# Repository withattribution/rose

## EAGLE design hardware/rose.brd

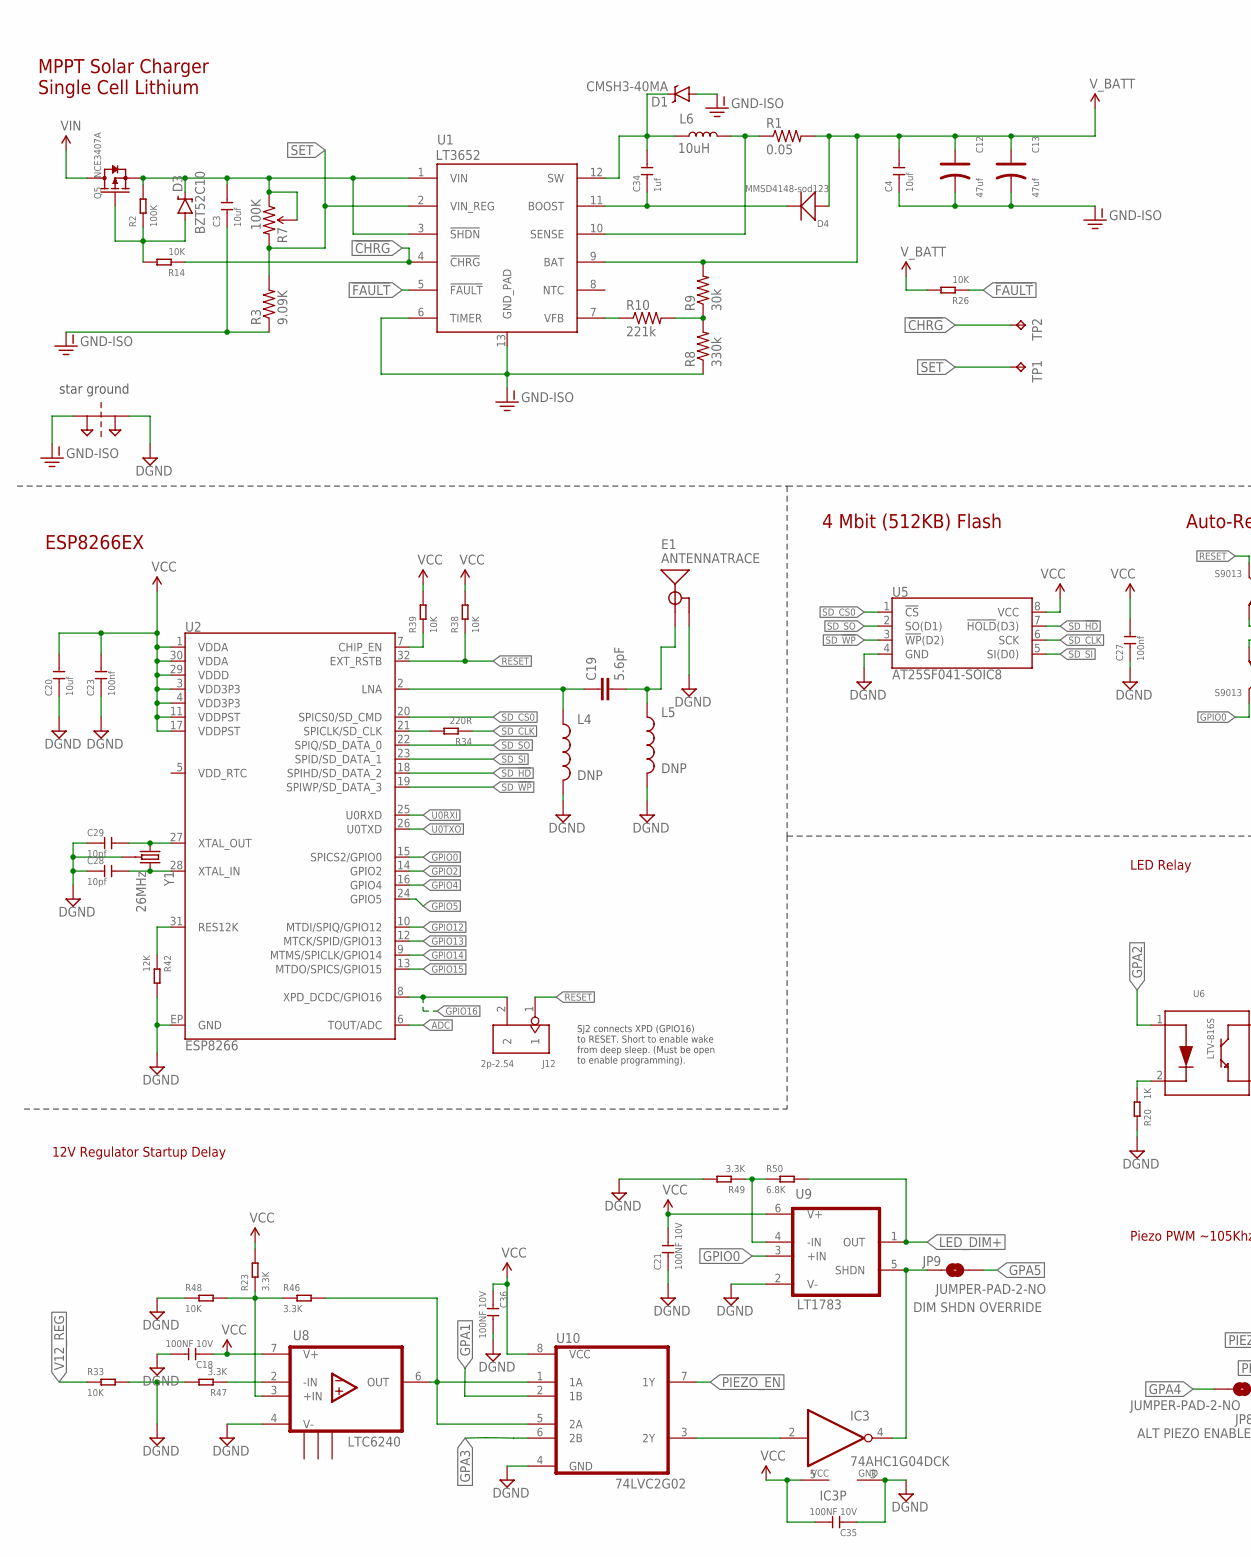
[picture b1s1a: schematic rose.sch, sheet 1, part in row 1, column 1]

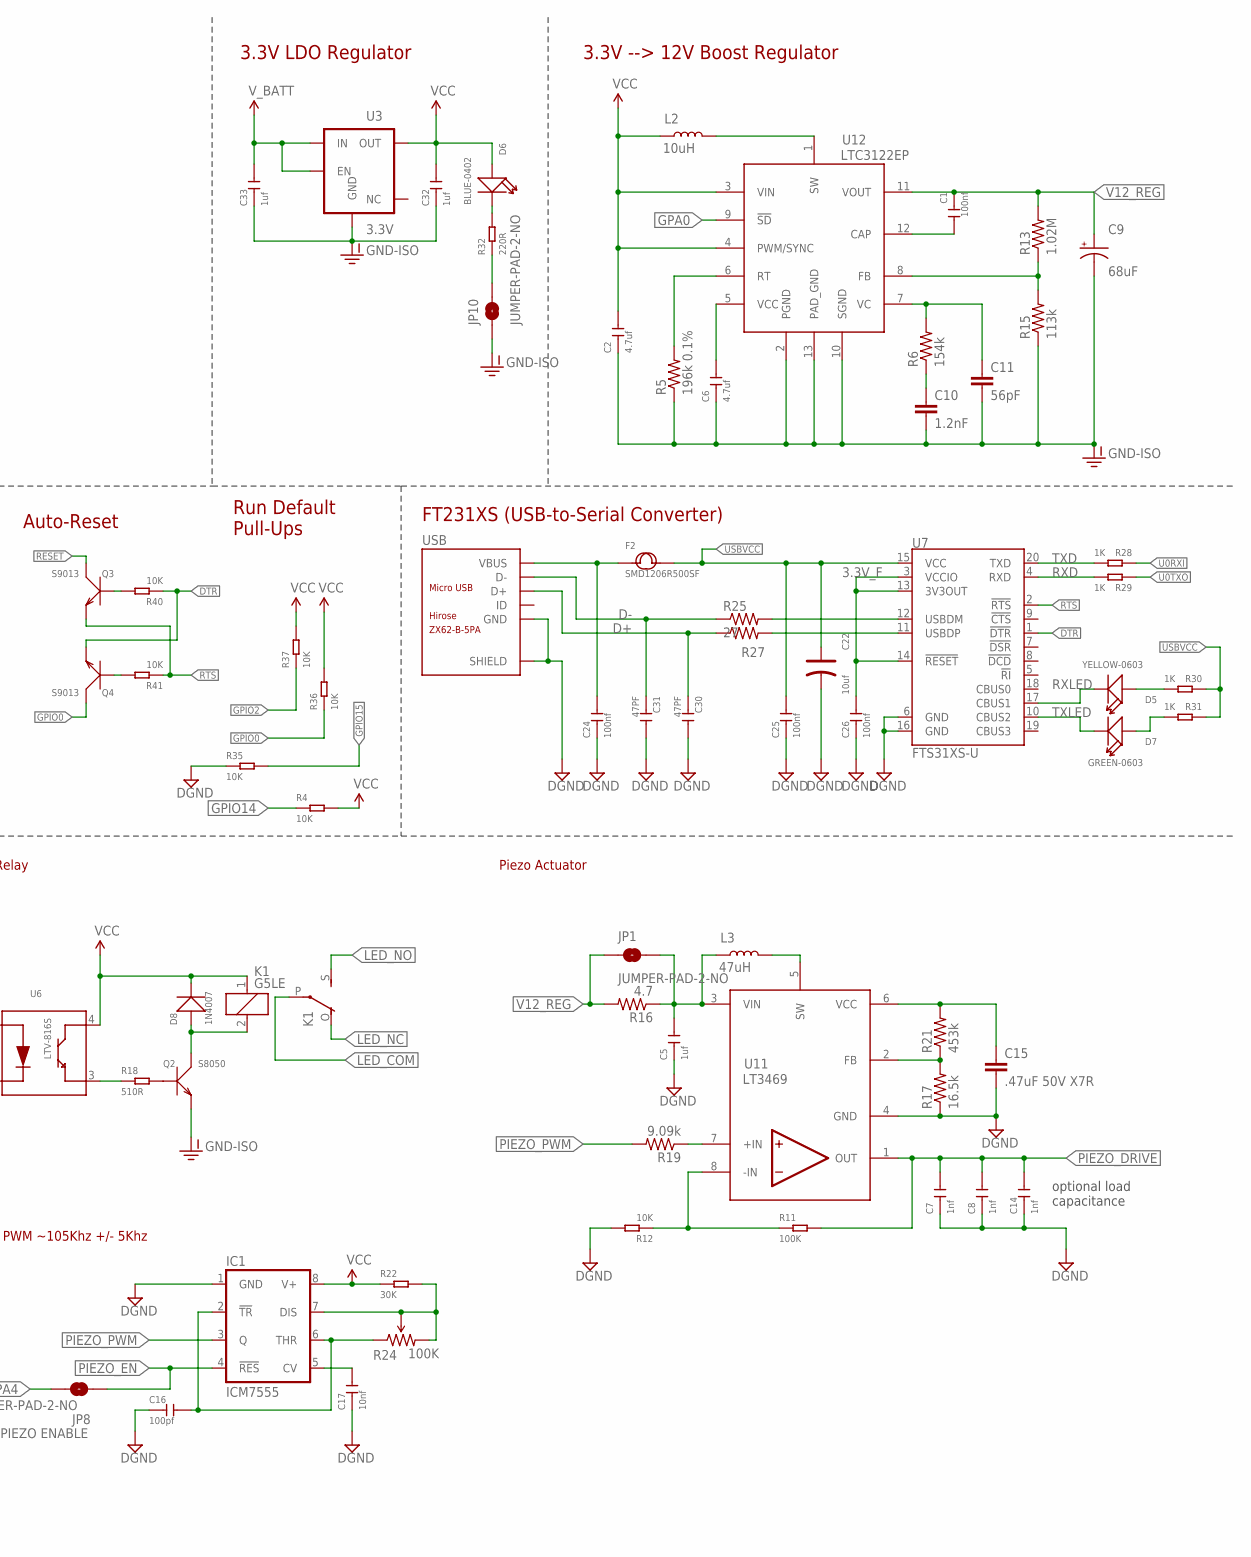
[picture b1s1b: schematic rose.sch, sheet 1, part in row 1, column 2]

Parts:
C1, C23, C24, C25, C26, C27: 100nf; C0402
C2, C6: 4.7uf; C0603
C3, C4: 10uf; C0805
C5, C32, C33, C34: 1uf; C0603
C7, C8, C14: 1nf; C0402
C9: 68uF; EIA6032
C10: 1.2nF; 0603-CAP
C11: 56pF; 0603-CAP
C12, C13: 47uf; AVX-C
C15: .47uF 50V X7R; 0603-CAP
C16: 100pf; C0603
C17: 10nf; C0402
C18, C21, C35, C36: 100NF 10V; C0402
C19: 5.6pF; 0603-CAP
C20: 10uf; C0402
C22: 10uf; AVX-A
C28, C29: 10pf; C0402
C30, C31: 47PF; C0402
D1: CMSH3-40MA; SMA-DIODE
D3: BZT52C10; SOD-123
D4: MMSD4148-sod123; SOD-123
D5: YELLOW-0603; LED-0603
D6: BLUE-0402; LED-0402
D7: GREEN-0603; LED-0603
D8: 1N4007; DO-214AC
E1: ANTENNATRACE; TRACE_ANTENNA_2.4GHZ_25.7MM
F2: SMD1206R500SF; F1206
IC1: ICM7555; SO08
IC3: 74AHC1G04DCK; SC70-5
J12: 2p-2.54; H2-2.54
JP1, JP8, JP9, JP10: JUMPER-PAD-2-NO; PAD-JUMPER-2-NO_NO_SILK
K1: G5LE
L2, L6: 10uH; SRR1240
L3: 47uH; SRR1240
L4, L5: DNP; 0603
PT1: 2PT_GND_TIE
Q2: S8050; SOT-23
Q3, Q4: S9013; SOT-23
Q5: NCE3407A; SOT-23
R1: 0.05; 1206
R2, R11: 100K; R0603
R3: 9.09K; 0603-RES
R4, R12, R14, R26, R33, R35, R36, R37, R38, R39, R40, R41, R48: 10K; R0603
R5: 196k 0.1%; 0603-RES
R6: 154k; 0603-RES
R7, R24: 100K; ST4ETA
R8: 330k; 0603-RES
R9: 30k; 0603-RES
R10: 221k; 0603-RES
R13: 1.02M; 0603-RES
R15: 113k; 0603-RES
R16: 4.7; 0603-RES
R17: 16.5k; 0603-RES
R18: 510R; R0603
R19: 9.09k; 0603-RES
R20, R28, R29, R30, R31: 1K; R0603
R21: 453k; 0603-RES
R22: 30K; R0603
R23, R46, R47, R49: 3.3K; R0603
R25, R27: 27; 0603-RES
R32, R34: 220R; R0603
R42: 12K; R0603
R50: 6.8K; R0603
TP1, TP2: TPTP10SQ; TP10SQ
U1: LT3652; MSOP-12_GND
U2: ESP8266; QFN32
U3: 3.3V; SOT23-5
U5: AT25SF041-SOIC8; SO08
U6: LTV-816S; SMD4-2.54-4.6X6.5MM
U7: FTS31XS-U; SSOP20_L
U8: LTC6240; SOIC-8
U9: LT1783; TSOT-23-6
U10: 74LVC2G02; TSSOP-8
U11: LT3469; TSOT-23-8
U12: LTC3122EP; 12MSOP
USB: ZX62-B-5PA; MICRO-USB5+6P-SMD-0.65-AB
Y1: 26MHz; CRYSTAL-SMD-3.2X2.5

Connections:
3.3V_F: C26.2, U7.3 (VCCIO), U7.13 (3V3OUT), U7.14 (!RESET)
!CHRG: R14.1, TP2.TP, U1.4 (!CHRG)
!FAULT: R26.1, U1.5 (!FAULT)
ADC: U2.6 (TOUT/ADC); also elsewhere on the board
BOOST: C34.1, D4.-, U1.11 (BOOST)
CHIP_EN: R39.1, U2.7 (CHIP_EN)
D+: C30.1, R27.1, USB.3 (D+)
D-: C31.1, R25.1, USB.2 (D-)
DGND: C5.1, C7.1, C8.1, C14.1, C15.2, C16.1, C17.1, C18.2, C20.1, C21.1, C22.-, C23.1, C24.1, C25.1, C26.1, C27.1, C28.1, C29.1, C30.2, C31.2, C35.1, C36.2, E1.GND, E1.GND2 (GND), IC1.1 (GND), IC3.3 (GND), L4.2, L5.2, PT1.P$2, R12.2, R17.1, R20.2, R33.2, R35.1, R42.2, R47.2, R48.1, R49.2, U2.EP (GND), U5.4 (GND), U7.6 (GND), U7.16 (GND), U8.4 (V-), U9.2 (V-), U10.4 (GND), U11.4 (GND), USB.5 (GND), USB.P1 (SHIELD), USB.P2 (SHIELD), USB.P3 (SHIELD), USB.P4 (SHIELD), USB.P5 (SHIELD), USB.P6 (SHIELD), Y1.2 (GND), Y1.4 (GND); also elsewhere on the board
DTR: Q4.2 (E), R40.1, U7.1 (!DTR)
FB: R8.2, R9.1, R10.2
GND-ISO: C2.1, C3.1, C4.1, C6.1, C9.P$2 (-), C10.2, C11.2, C12.-, C13.-, C32.1, C33.1, D1.A, JP10.1, PT1.P$1, Q2.2 (E), R3.1, R5.1, R8.1, R15.1, U1.6 (TIMER), U1.13 (GND_PAD), U3.2 (GND), U12.2 (PGND), U12.10 (SGND), U12.13 (PAD_GND); also elsewhere on the board
GPA0: U12.9 (!SD); also elsewhere on the board
GPA1: U10.2 (1B); also elsewhere on the board
GPA2: U6.1 (ANODE); also elsewhere on the board
GPA3: U10.6 (2B); also elsewhere on the board
GPA4: JP8.1; also elsewhere on the board
GPA5: JP9.1; also elsewhere on the board
GPIO0: Q4.3 (C), R36.1, U2.15 (SPICS2/GPIO0), U9.3 (+IN)
GPIO2: R37.1, U2.14 (GPIO2); also elsewhere on the board
GPIO4: U2.16 (GPIO4); also elsewhere on the board
GPIO5: U2.24 (GPIO5); also elsewhere on the board
GPIO12: U2.10 (MTDI/SPIQ/GPIO12); also elsewhere on the board
GPIO13: U2.12 (MTCK/SPID/GPIO13); also elsewhere on the board
GPIO14: R4.1, U2.9 (MTMS/SPICLK/GPIO14); also elsewhere on the board
GPIO15: R35.2, U2.13 (MTDO/SPICS/GPIO15); also elsewhere on the board
GPIO16: J12.2, U2.8 (XPD_DCDC/GPIO16)
LED_COM: K1.P; also elsewhere on the board
LED_DIM+: R50.2, U9.1 (OUT); also elsewhere on the board
LED_NC: K1.O; also elsewhere on the board
LED_NO: K1.S; also elsewhere on the board
LNA: C19.1, L4.1, U2.2 (LNA)
LNA2: C19.2, E1.ANT (SIGNAL), L5.1
unnamed: R42.1, U2.31 (RES12K)
unnamed: C3.2, D3.C, Q5.2 (S), R2.2, R7.P$1 (CCW), R7.P$2 (WIPER), U1.1 (VIN), U1.3 (!SHDN)
unnamed: R10.1, U1.7 (VFB)
unnamed: R20.1, U6.2 (CATHODE)
unnamed: D3.A, Q5.1 (G), R2.1, R14.2
unnamed: IC1.7 (DIS), R22.2, R24.P$2 (WIPER), R24.P$3 (CW)
unnamed: C28.2, U2.28 (XTAL_IN), Y1.3 (2)
unnamed: D8.1 (+), K1.2, Q2.3 (C)
unnamed: C16.2, IC1.2 (!TR), IC1.6 (THR), R24.P$1 (CCW)
unnamed: R18.1, U6.3 (EMITER)
unnamed: C17.2, IC1.5 (CV)
unnamed: Q2.1 (B), R18.2
unnamed: C29.2, U2.27 (XTAL_OUT), Y1.1
unnamed: L2.P$2 (2), U12.1 (SW)
unnamed: R5.2, U12.6 (RT)
unnamed: C6.2, U12.5 (VCC)
unnamed: R46.2, U8.6 (OUT), U10.1 (1A), U10.5 (2A)
unnamed: C1.2, U12.12 (CAP)
unnamed: C11.1, R6.2, U12.7 (VC)
unnamed: R13.1, R15.2, U12.8 (FB)
unnamed: C10.1, R6.1
unnamed: L3.P$2 (2), U11.5 (SW)
unnamed: C5.2, JP1.2, L3.P$1 (1), R16.1, U11.3 (VIN)
unnamed: R11.1, R12.1, U11.8 (-IN)
unnamed: R19.1, U11.7 (+IN)
unnamed: C15.1, R21.2, U11.6 (VCC)
unnamed: R17.2, R21.1, U11.2 (FB)
unnamed: D7.+, R31.1
unnamed: D5.+, R30.1
unnamed: R25.2, U7.12 (USBDM)
unnamed: R27.2, U7.11 (USBDP)
unnamed: D6.-, R32.2
unnamed: JP10.2, R32.1
unnamed: Q3.1 (B), R40.2
unnamed: Q4.1 (B), R41.2
unnamed: R23.1, R46.1, R48.2, U8.3 (+IN)
unnamed: R47.1, U8.2 (-IN)
unnamed: R49.1, R50.1, U9.4 (-IN)
unnamed: IC3.2 (I), U10.3 (2Y)
unnamed: IC3.4 (O), JP9.2, U9.5 (SHDN)
PIEZO_DRIVE: C7.2, C8.2, C14.2, R11.2, U11.1 (OUT); also elsewhere on the board
PIEZO_EN: IC1.4 (!RES), JP8.2, U10.7 (1Y)
PIEZO_PWM: IC1.3 (Q), R19.2
RESET: J12.1, Q3.3 (C), R38.1, U2.32 (EXT_RSTB)
RTS: Q3.2 (E), R41.1, U7.2 (!RTS)
RXD: R29.1, U7.4 (RXD)
RXLED: D5.-, U7.17 (CBUS1)
SD_!HD!: U2.18 (SPIHD/SD_DATA_2), U5.7 (!HOLD!(D3))
SD_!WP!: U2.19 (SPIWP/SD_DATA_3), U5.3 (!WP!(D2))
SD_CLK: R34.1, U5.6 (SCK)
SD_CLK0: R34.2, U2.21 (SPICLK/SD_CLK)
SD_CS0: U2.20 (SPICS0/SD_CMD), U5.1 (!CS!)
SD_SI: U2.23 (SPID/SD_DATA_1), U5.5 (SI(D0))
SD_SO: U2.22 (SPIQ/SD_DATA_0), U5.2 (SO(D1))
SENSE: L6.P$2 (2), R1.1, U1.10 (SENSE)
SET: R3.2, R7.P$3 (CW), TP1.TP, U1.2 (VIN_REG)
SW: C34.2, D1.C, L6.P$1 (1), U1.12 (SW)
TXD: R28.1, U7.20 (TXD)
TXLED: D7.-, U7.10 (CBUS2)
U0RXI: R28.2, U2.25 (U0RXD); also elsewhere on the board
U0TXO: R29.2, U2.26 (U0TXD); also elsewhere on the board
USBVCC: C22.+, C25.2, F2.2, R30.2, R31.2, U7.15 (VCC)
V12_REG: C1.1, C9.P$1 (+), JP1.1, R13.2, R16.2, R33.1, U12.11 (VOUT); also elsewhere on the board
VBUS: C24.2, F2.1, USB.1 (VBUS)
VCC: C2.2, C18.1, C20.2, C21.2, C23.2, C27.2, C32.2, C35.2, C36.1, D6.+, D8.2 (-), IC1.8 (V+), IC3.5 (VCC), K1.1, L2.P$1 (1), R4.2, R22.1, R23.2, R36.2, R37.2, R38.2, R39.2, U2.1 (VDDA), U2.3 (VDD3P3), U2.4 (VDD3P3), U2.11 (VDDPST), U2.17 (VDDPST), U2.29 (VDDD), U2.30 (VDDA), U3.5 (OUT), U5.8 (VCC), U6.4 (COLLECTOR), U8.7 (V+), U9.6 (V+), U10.8 (VCC), U12.3 (VIN), U12.4 (PWM/SYNC); also elsewhere on the board
VIN: Q5.3 (D); also elsewhere on the board
V_BATT: C4.2, C12.+, C13.+, C33.2, D4.+, R1.2, R9.2, R26.2, U1.9 (BAT), U3.1 (IN), U3.3 (EN); also elsewhere on the board

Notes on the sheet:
optional load capacitance
FT231XS (USB-to-Serial Converter)
Auto-Reset
Run Default Pull-Ups
SJ2 connects XPD (GPIO16) to RESET. Short to enable wake from deep sleep. (Must be open to enable programming).
MPPT Solar Charger Single Cell Lithium
3.3V LDO Regulator
3.3V --> 12V Boost Regulator
ESP8266EX
4 Mbit (512KB) Flash
Piezo PWM ~105Khz +/- 5Khz
LED Relay
12V Regulator Startup Delay
Piezo Actuator
star ground
DIM SHDN OVERRIDE
ALT PIEZO ENABLE

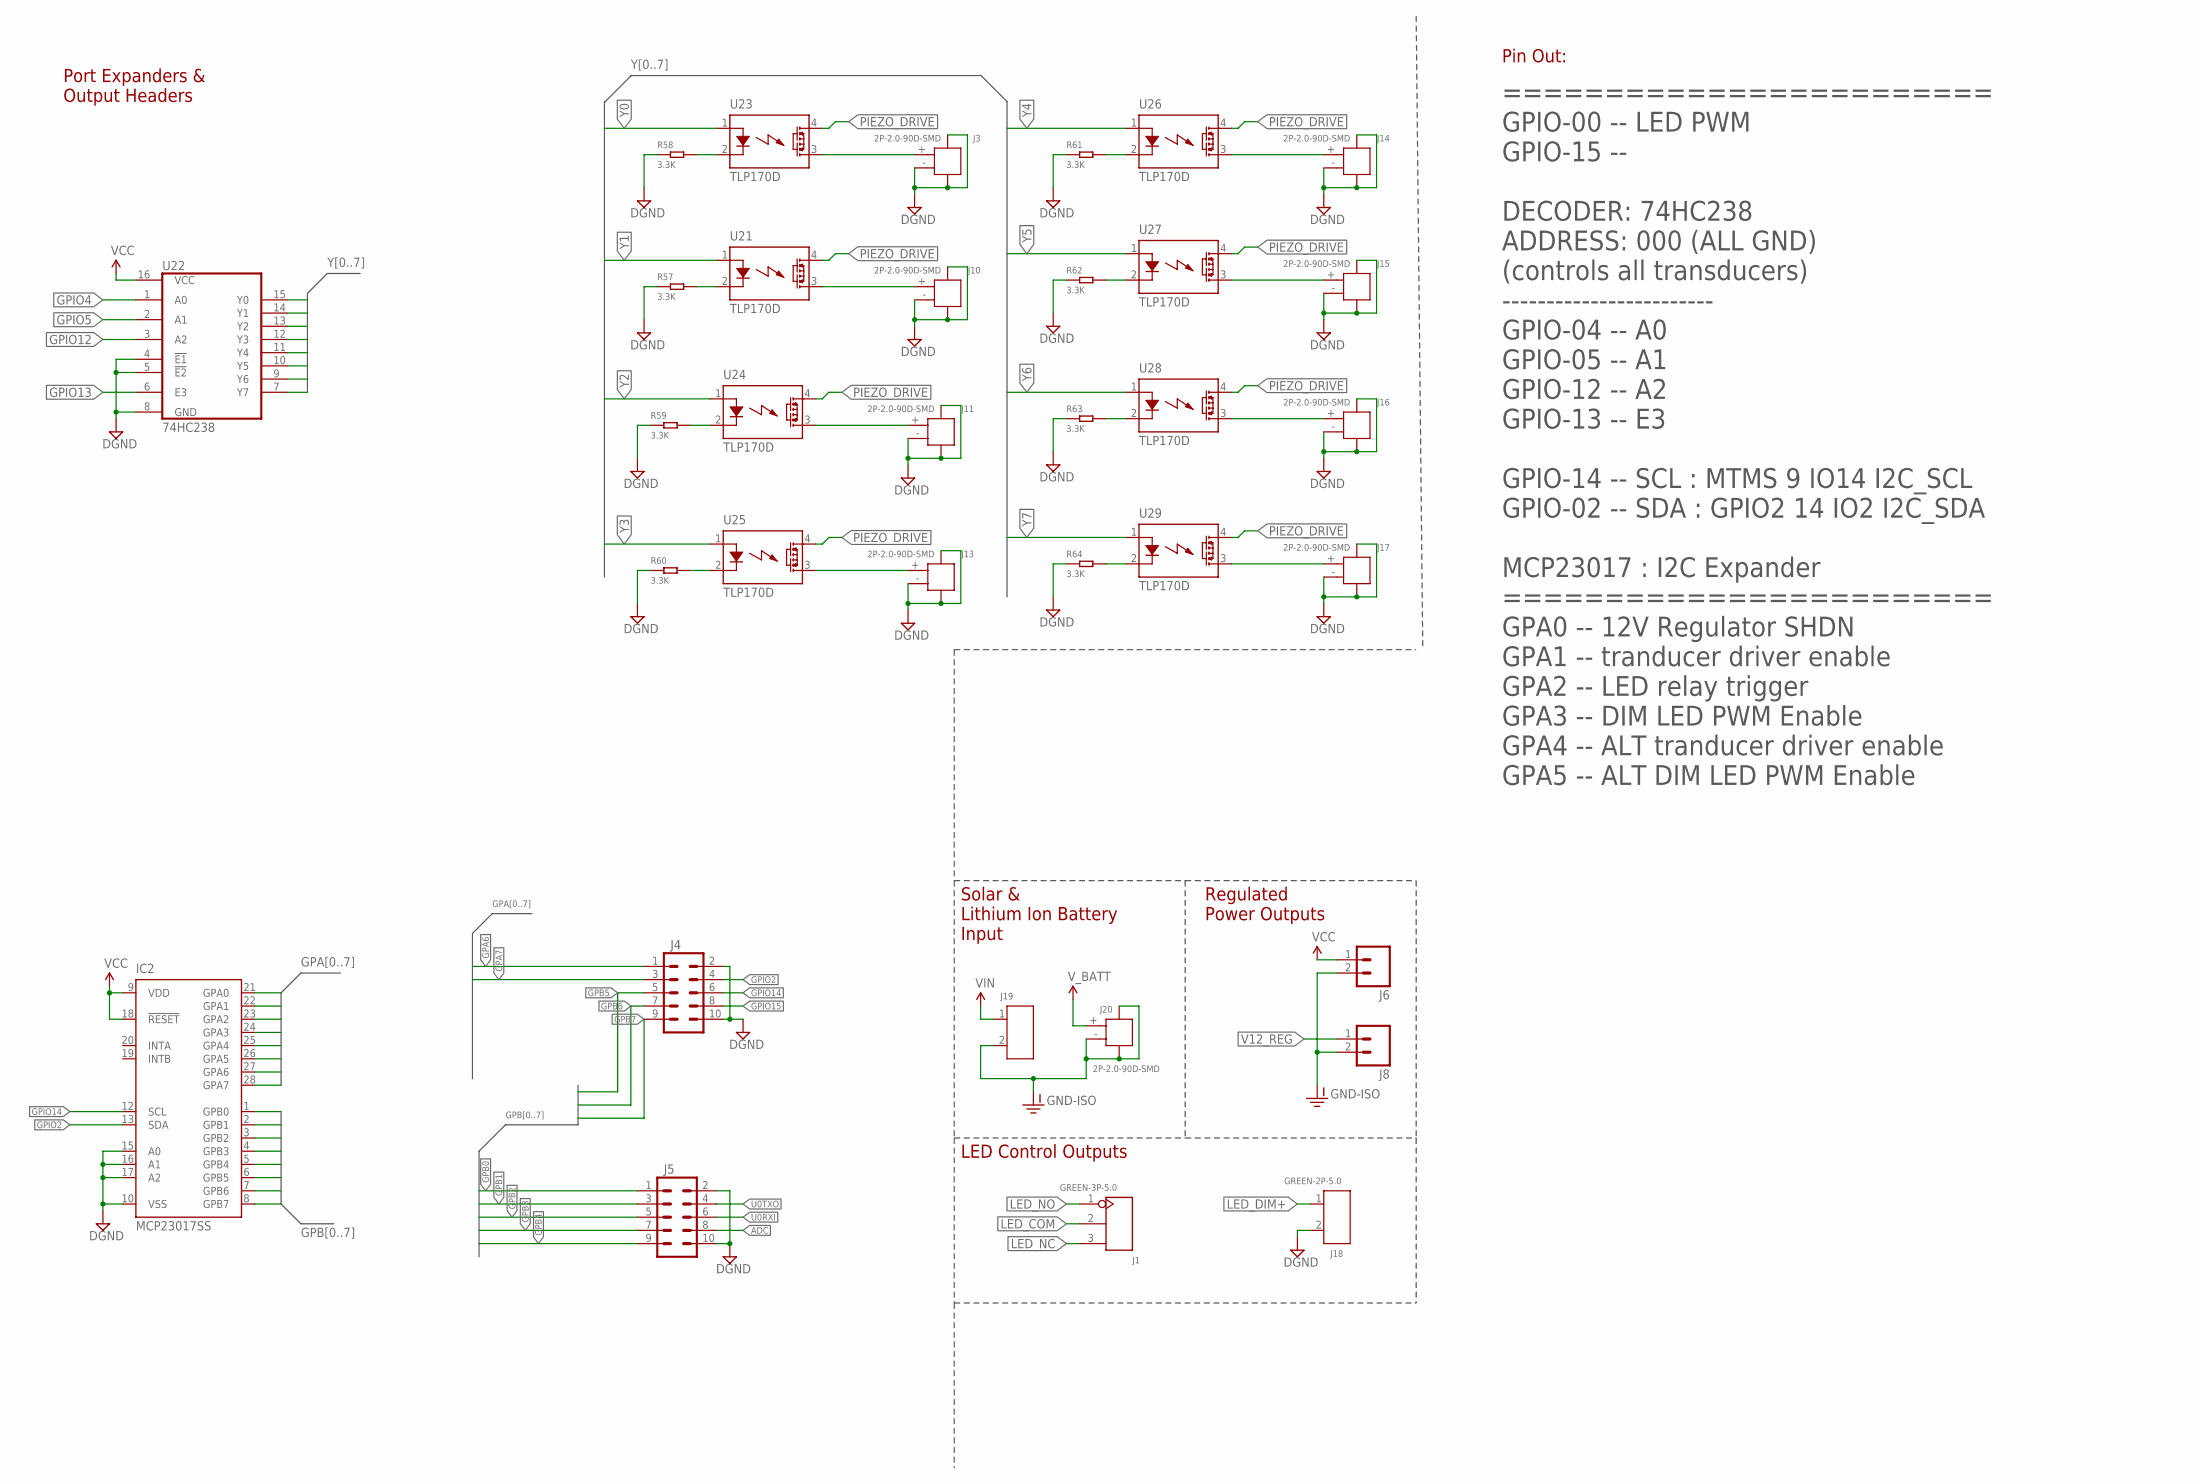
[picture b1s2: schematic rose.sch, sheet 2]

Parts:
IC2: MCP23017SS; SSOP28
J1: GREEN-3P-5.0; H3-5.0-15.5X8.0MM
J3, J10, J11, J13, J14, J15, J16, J17, J20: 2P-2.0-90D-SMD; HW2-SMD-2.0-90D
J4, J5: M05X2NO_SILK; 2X5_NOSILK
J6, J8: M02PTH; 1X02
J18, J19: GREEN-2P-5.0; H2-5.0-10.5X8.0MM
R57, R58, R59, R60, R61, R62, R63, R64: 3.3K; R0603
U21, U23, U24, U25, U26, U27, U28, U29: TLP170D; 4-SOP
U22: 74HC238; TSSOP-16

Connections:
ADC: J5.8; also elsewhere on the board
DGND: IC2.10 (VSS), IC2.15 (A0), IC2.16 (A1), IC2.17 (A2), J3.3, J3.4, J3.- (2), J4.2, J4.10, J5.2, J5.10, J10.3, J10.4, J10.- (2), J11.3, J11.4, J11.- (2), J13.3, J13.4, J13.- (2), J14.3, J14.4, J14.- (2), J15.3, J15.4, J15.- (2), J16.3, J16.4, J16.- (2), J17.3, J17.4, J17.- (2), J18.2, R57.1, R58.1, R59.1, R60.1, R61.1, R62.1, R63.1, R64.1, U22.4 (!E1), U22.5 (!E2), U22.8 (GND); also elsewhere on the board
GND-ISO: J6.2, J8.2, J19.2, J20.3, J20.4, J20.- (2); also elsewhere on the board
GPA0: IC2.21 (GPA0); also elsewhere on the board
GPA1: IC2.22 (GPA1); also elsewhere on the board
GPA2: IC2.23 (GPA2); also elsewhere on the board
GPA3: IC2.24 (GPA3); also elsewhere on the board
GPA4: IC2.25 (GPA4); also elsewhere on the board
GPA5: IC2.26 (GPA5); also elsewhere on the board
GPA6: IC2.27 (GPA6), J4.1
GPA7: IC2.28 (GPA7), J4.3
GPB0: IC2.1 (GPB0), J5.1
GPB1: IC2.2 (GPB1), J5.3
GPB2: IC2.3 (GPB2), J5.5
GPB3: IC2.4 (GPB3), J5.7
GPB4: IC2.5 (GPB4), J5.9
GPB5: IC2.6 (GPB5), J4.5
GPB6: IC2.7 (GPB6), J4.7
GPB7: IC2.8 (GPB7), J4.9
GPIO2: IC2.13 (SDA), J4.4; also elsewhere on the board
GPIO4: U22.1 (A0); also elsewhere on the board
GPIO5: U22.2 (A1); also elsewhere on the board
GPIO12: U22.3 (A2); also elsewhere on the board
GPIO13: U22.6 (E3); also elsewhere on the board
GPIO14: IC2.12 (SCL), J4.6; also elsewhere on the board
GPIO15: J4.8; also elsewhere on the board
LED_COM: J1.2; also elsewhere on the board
LED_DIM+: J18.1; also elsewhere on the board
LED_NC: J1.3; also elsewhere on the board
LED_NO: J1.1; also elsewhere on the board
unnamed: J10.+ (1), U21.3 (DS2)
unnamed: R57.2, U21.2 (K)
unnamed: J11.+ (1), U24.3 (DS2)
unnamed: R59.2, U24.2 (K)
unnamed: J3.+ (1), U23.3 (DS2)
unnamed: R58.2, U23.2 (K)
unnamed: J13.+ (1), U25.3 (DS2)
unnamed: R60.2, U25.2 (K)
unnamed: J14.+ (1), U26.3 (DS2)
unnamed: R61.2, U26.2 (K)
unnamed: J15.+ (1), U27.3 (DS2)
unnamed: R62.2, U27.2 (K)
unnamed: J16.+ (1), U28.3 (DS2)
unnamed: R63.2, U28.2 (K)
unnamed: J17.+ (1), U29.3 (DS2)
unnamed: R64.2, U29.2 (K)
PIEZO_DRIVE: U21.4 (DS1), U23.4 (DS1), U24.4 (DS1), U25.4 (DS1), U26.4 (DS1), U27.4 (DS1), U28.4 (DS1), U29.4 (DS1); also elsewhere on the board
U0RXI: J5.6; also elsewhere on the board
U0TXO: J5.4; also elsewhere on the board
V12_REG: J8.1; also elsewhere on the board
VCC: IC2.9 (VDD), IC2.18 (!RESET), J6.1, U22.16 (VCC); also elsewhere on the board
VIN: J19.1; also elsewhere on the board
V_BATT: J20.+ (1); also elsewhere on the board
Y0: U22.15 (Y0), U23.1 (A)
Y1: U21.1 (A), U22.14 (Y1)
Y2: U22.13 (Y2), U24.1 (A)
Y3: U22.12 (Y3), U25.1 (A)
Y4: U22.11 (Y4), U26.1 (A)
Y5: U22.10 (Y5), U27.1 (A)
Y6: U22.9 (Y6), U28.1 (A)
Y7: U22.7 (Y7), U29.1 (A)

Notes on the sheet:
======================== GPIO-00 -- LED PWM GPIO-15 -- DECODER: 74HC238 ADDRESS: 000 (ALL GND) (controls all transducers) ------------------------ GPIO-04 -- A0 GPIO-05 -- A1 GPIO-12 -- A2 GPIO-13 -- E3 GPIO-14 -- SCL : MTMS 9 IO14 I2C_SCL GPIO-02 -- SDA : GPIO2 14 IO2 I2C_SDA MCP23017 : I2C Expand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
Solar & Lithium Ion Battery Input
LED Control Outputs
Port Expanders & Output Headers
Regulated Power Outputs
Pin Out:

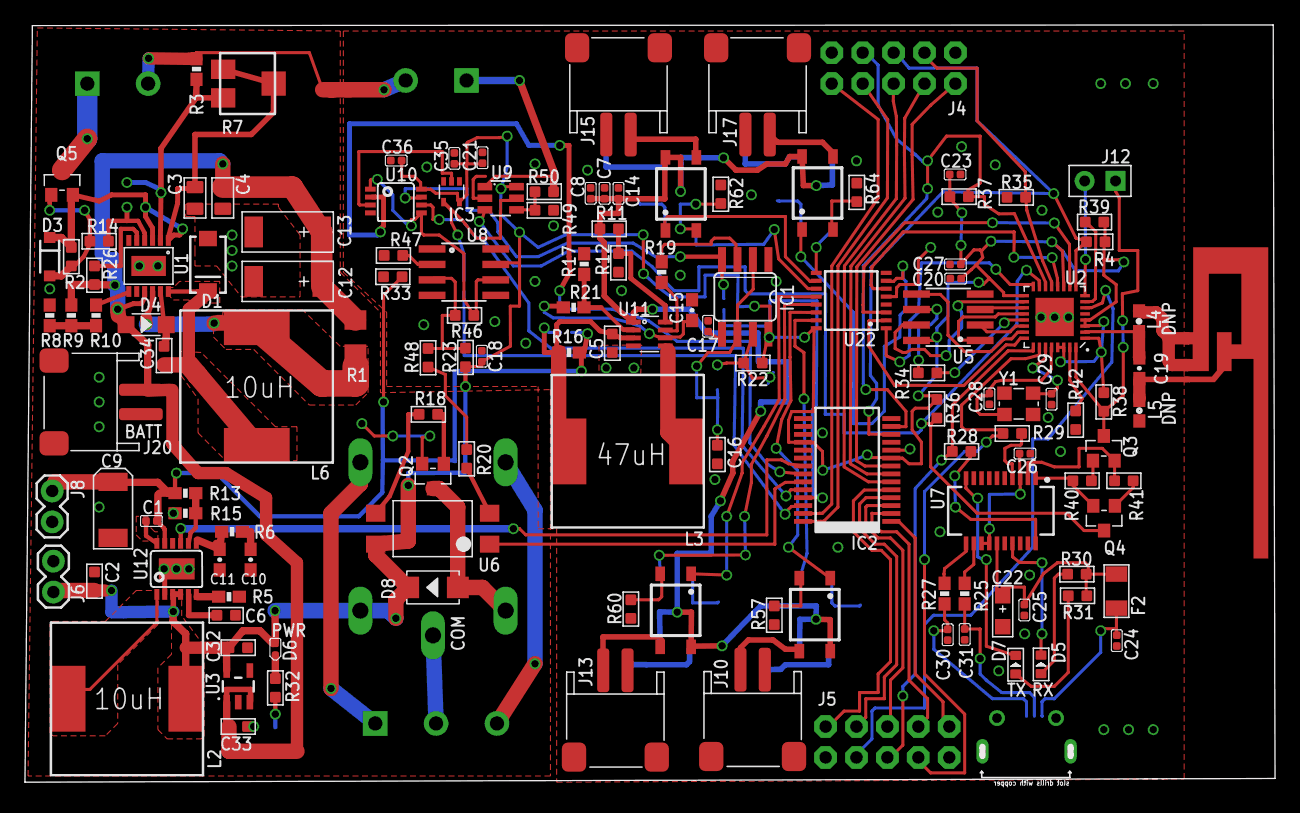
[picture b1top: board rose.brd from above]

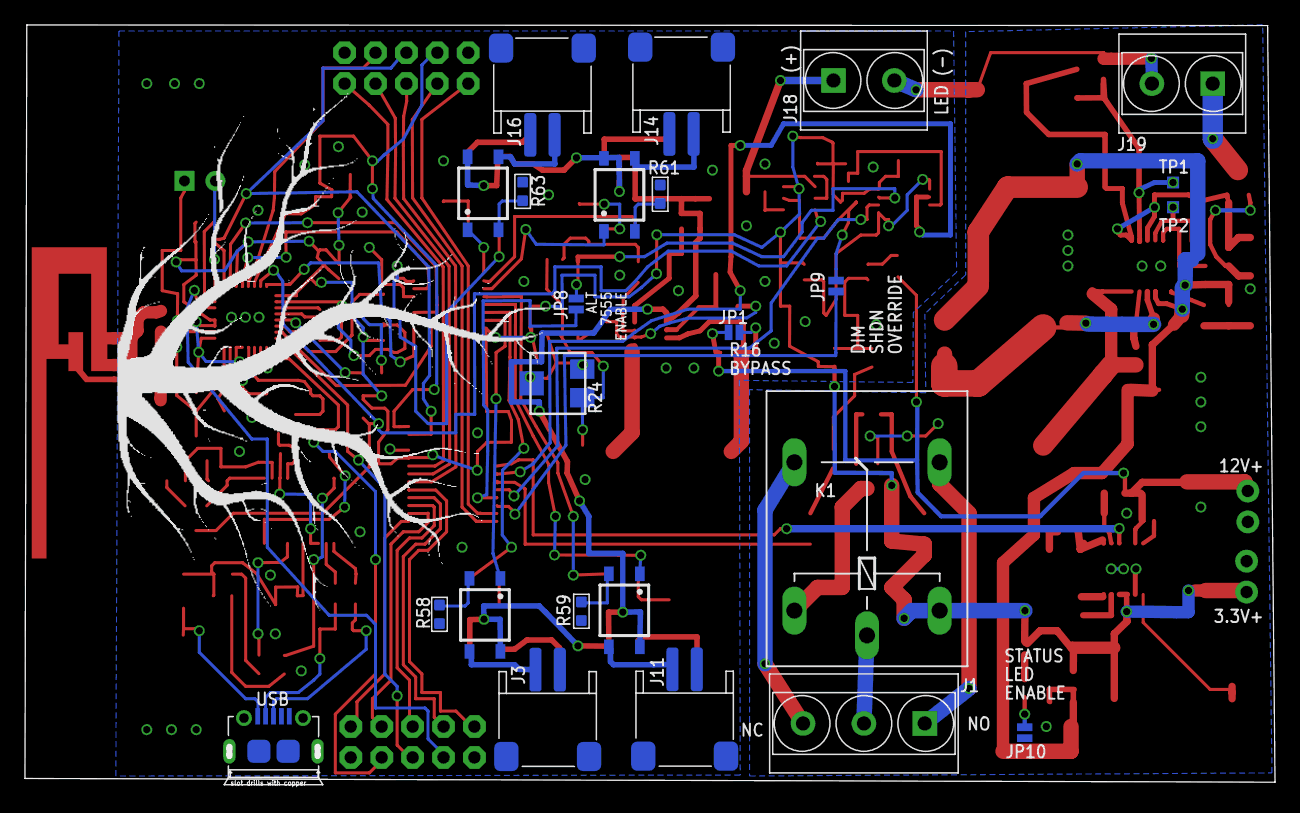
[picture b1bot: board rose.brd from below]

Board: 2 copper layers, 102.3 x 62.3 mm, 160 parts (24 on the bottom side), 134 nets.

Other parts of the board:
U$1: LEAF

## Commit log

2016-06-25 rev A out for production: initial commit
2016-06-25 adding external part digikey links
2017-06-19 modified schmitt trigger for future rev
2025-10-31 adding a basic piezo driver osx ltspice simulation
2025-10-31 Add SPICE model for piezo driver circuit
    This file defines a SPICE model for a piezo driver circuit, including user parameters, drive settings, and measurements for analysis.
2025-10-31 remove binary driver.cir
2025-11-10 adding fulling verified working piezo driver simulation
2025-11-10 modified driver simulation with in-stock RDRV resistor pair and other working parts with links
2025-11-11 adding driver BOM without hbridge components
2025-11-11 modified BOM markdown with properly calculated R_SENSE expected measured voltages
2025-11-11 updated bom v1.0
2025-11-17 hbridge and driver power boms

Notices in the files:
parts and their libraries:
SparkFun-Capacitors: Licensing: CC v3.0 Share-Alike You are welcome to use this library for commercial purposes.
SparkFun-RF: Licensing: Creative Commons ShareAlike 4.0 International - https://creativecommons.org/licenses/by-sa/4.0
